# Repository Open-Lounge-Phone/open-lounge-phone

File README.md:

# Open Lounge Phone

A free, open-source, screen-free phone. Real mechanical keys, a handset, and nothing else: no
browser, no feeds, no strangers.

It is a lot more than one phone. Everything runs on **connections**: you sign in on a public
hub you trust, or federate your own servers and services, and you choose the level of safety and
security you want at every step, including how available and how visible you are to each person.
The same board and software make a kid's first phone, a desk phone for grown-ups, a shared
Lounge phone, a small office phone system, or (with the labs firmware) a house intercom, a
doorbell and an elder's daily check-in.

- **Kids' phone** — calls only the contacts a guardian approves, respects quiet hours (callers
  get voicemail with a transcript instead of waking anyone up), and its guardian sees when it
  was last online. Kids' phones on the market are closed boxes with a fixed feature list; this
  one is open, so a child can learn how it works and tinker with it as they grow, while the
  phone's rules stay with their guardians until they decide otherwise. When it starts running
  firmware that isn't an official update, its guardians hear about it straight away, and with
  Ask me first it waits for their OK.
- **Voicemail everywhere** — any call that isn't answered (no answer, declined, busy, quiet
  hours, unavailable) goes to a greeting — the standard one, your recorded name, or your own —
  and the message lands in the callee's inbox, across servers too.
- **Lounge phone** — a shared phone anyone in the space takes over as themselves by scanning its
  code and pressing the key it flashes; it forgets them the moment they're done. People from
  other servers can use it too, if the space allows guests.
- **Grown-ups** use the companion app on their own phone or computer, or any old device as a
  phone (`/device/`, add it to the home screen). You choose who can reach you, whether you're
  taking calls right now, and whether your connections see that you're around.
- **Not just a phone** — the labs firmware ([firmware/labs/](firmware/labs/README.md), 0.0.0)
  turns the board into a house intercom, a doorbell or front desk, a dinner's-ready chime, a
  daily check-in for an elder, a Home Assistant panel, a dial-a-story line or a USB macro pad.
  It's the build on the v0.1 dev boards for now (lightly tested; most of its extras so far on a
  computer). Its features come to the phone firmware later, where they make sense.

Run it on **your own Cloudflare account** or **self-host it with Docker**; to just try it, use the
free public hub at [hub.openloungephone.app](https://hub.openloungephone.app). Your keys and your
server are yours: nothing depends on this project ([security model](docs/security-model.md)). Servers connect to each other, so everyone can reach everyone: you
knock on someone's address (`name@server`), and once they accept you can call. Nobody —
including this project — sits in the middle of your calls, and there is no bridge to the phone
network, ever.

## Status

The software works end to end today. The hardware has its first **early dev board prototype**:
[hardware v0.1](https://github.com/Open-Lounge-Phone/open-lounge-phone/releases/tag/hw-v0.1) (rev A), ordered from JLCPCB on 2026-09-30. Its files are in that release. **Board v0.3 is coming soon** as a fully assembled board or a bare PCB; [join the interest list](https://github.com/Open-Lounge-Phone/open-lounge-phone/discussions/1).

| Phase | What | State |
|---|---|---|
| M0–M4 | Protocol and core logic; self-hosted server, browser phone, companion app; Cloudflare backend; invites, passkeys, voicemail with transcripts | done |
| Lounge | QR takeover with a key-press proof, ephemeral sessions, "open to chat" | done (software) |
| Security (software) | Four-word device fingerprint (phone MENU → About, pairing, the phone's page); phone page with last seen, software version and remove-and-wipe; retention defaults and transcription on/off per space; an audit trail in every space (who changed what, never what was said; read only by those who run the space) | done (software) |
| Recording (C2) | Opt-in per space (never with kids' phones), always announced to every party (spoken prompt, the phone's status light and `REC` on its display, a mark in the apps, other servers too), made by the recording side's own client and uploaded, in the timeline and call log, transcribed only where the space transcribes, expiring with history; other servers may refuse recorded calls | done (software) |
| Device lifecycle | Modes at claim (kids, personal desk phone, Lounge); per-space Lounge session length (idle, end of day, until logout); optional house-line keys and "who's here" on idle Lounge phones (off by default; public lines only for someone signed in); a space's name and time zone can be changed later (Settings), and the phones follow at once; remove = the phone wipes itself | done (server, apps, browser phone); firmware: remove = wipe done, modes and factory reset later |
| P1 / P1b | Accounts and handles (`name@server`), several households per account, open sign-up; spaces (home, team, organization); handles reserved 90 days; recovery codes, session list and sign out everywhere, space owners and leaving (0.5.0) | done |
| P2 | Connections ("buddies"): knock, accept, decline, block — on one server and across servers (signed server-to-server requests) | done |
| P3 | Calls across servers, voicemail, opt-in presence, Lounge guests from other servers | done |
| P4 | The public hub: free, donation-funded, fair-use allowance, Turnstile, operator view, export and account deletion | **live** at hub.openloungephone.app (2026-09-29) |
| Voicemail everywhere | Unanswered calls go to voicemail for every caller and callee (people, kids' phones, Lounge guests, other servers); greetings (standard, recorded name, custom); ring time; recording the greeting on the phone | done (software) |
| P2b | Buddy timeline: per-connection history of calls and voicemails (with transcripts), expiring per connection or by your default (30 days / 1 year / forever); no text chat | done (software) |
| M5 | One-command CLI, `npx openloungephone`: `deploy cloudflare` (prompts, preflight, summary; keys never echoed), `selfhost init` (compose.yaml + .env with random secrets, optional coturn/LiveKit), `status <url>`, `doctor` | done; the desktop (Tauri) app was dropped — the installable web apps cover it |
| P3.5 | Rooms: party lines (always open, or at set hours that ring the members' phones at opening), phone rooms with addresses (`standup@host`, dialable from any phone's key), host mute/remove/lock, cross-server join; hold, instant 3-way (Add caller → Merge) and blind/attended transfer; a peer-to-peer mesh (≤ 4) or a relay (Cloudflare Realtime SFU, or LiveKit when self-hosting) with top-3 forwarding, idle drop and fair-use metering | done (software); relayed rooms are encrypted in transit, end-to-end (SFrame) planned |
| P6 (C1) | Team and org spaces as a workplace phone system: owner/admin/member roles, searchable directory, extensions (companion and phone MENU → Dial ext), ring groups (simultaneous, sequential, round robin), business hours with after-hours actions, shared voicemail boxes ("heard by"), call log with CSV export, audit trail, transfer across households and servers inside the space; public lines (a ring group with its own address anyone may call without connecting, with a queue, voicemail and "call me back"; a call back nobody took shows on the phones as a missed call) ([docs/workplace.md](docs/workplace.md)) | done (software) |
| Calls (0.7.0) | Mute on the phones (MENU 3) and M in the app; a mic check and microphone/speaker choice in the app; reconnecting with an ICE restart, a plain "connection lost" and a poor-connection note; call waiting; missed calls (kept per person or phone, on the phones' MENU 5 and the app's Home) with call back and redial ([docs/phone-ux.md](docs/phone-ux.md)) | done (server, apps, browser phone, firmware 0.9.4; firmware tried in QEMU, not yet on a real board) |
| Notices | A space's guardians (owner and admins in a team) post a short notice to its phones ("Bus is here"), with an optional recording: a chime and the text on the ready screen, lifting the handset plays it, a key clears it; it expires (an hour by default) ([docs/notices.md](docs/notices.md)) | done (server, apps, browser phone, firmware; not yet on a real board) |
| Add-ons | Any service that serves live voice over a call (an assistant, a radio, a notes taker), linked to your own account with an address on it, `you+radio@host`: it links like a phone pairs, says what it does (shown on its page in the app's Add-ons tab), and only you can call it at that address; parts it offers for sharing you give to people, who call that part at its own address `you+radio+listen@host` (here or on other servers) and can stop its calls or give it back. Every add-on is treated as untrusted: an allow-list of messages, limits on calls and lines, calls marked as an add-on's everywhere, kids' phones never reached; off unless the server's operator turns them on (`ADDONS=on`). The add-on bridge ([sdk/python](sdk/python/README.md), Python, Apache-2.0) gives a service the calls as events and PCM audio, with echo and one-way radio examples ([docs/add-ons.md](docs/add-ons.md)) | done (server, apps, browser phone, bridge, sharing; the hardware phone shows the label, not the share, and is not yet tested on a real board) |
| P5 | Interop tests in CI (two self-hosted servers and two Workers under `wrangler dev`, on every push) and a versioned federation spec, [docs/federation-spec.md](docs/federation-spec.md) | done |
| Versions | Servers advertise their software, federation versions and features and negotiate per peer (degrading in plain words); phones and servers exchange protocol ranges (`UPDATE NEEDED` on a too-old phone); v1 frozen by conformance vectors (`tests/conformance/`); CI runs this server against the previous release (`server-v*`) both ways | done |
| Firmware | ESP32-S3 firmware ([firmware/](firmware/README.md), ESP-IDF; changes in [firmware/CHANGELOG.md](firmware/CHANGELOG.md)): Wi-Fi and server setup from a phone, pairing, calls with two-way audio (Opus wideband, PCMU fallback, AGC, concealment, sidetone, echo measurement and canceller: [docs/audio.md](docs/audio.md)), leaving and playing voicemail, hold and transfer, extensions, Lounge phones, signed updates (off in source builds), encrypted storage, the phone check and self-test. The labs build ([firmware/labs/](firmware/labs/README.md), 0.0.0) adds the experiments above | 0.9.6: call audio (Opus at 16 kHz, the mic's AGC, an adaptive jitter buffer and concealment, sidetone, echo test and canceller). 0.9.5: the wired network on hw v0.2. 0.9.4: mute, call waiting, missed calls and redial, reconnecting; the house intercom (signed and encrypted on the LAN), the chime and the daily check-in moved in from labs. Host tests, builds and QEMU tests ([firmware/CHANGELOG.md](firmware/CHANGELOG.md)); not yet on a real board. The v0.1 dev boards run the experimental labs build (0.0.0) for now, lightly tested; full testing waits on the Wi-Fi antennas ([hardware/BRINGUP.md](hardware/BRINGUP.md)) |
| Hardware | A minimal 2-layer board (ESP32-S3, 12 hot-swap keys + hook switch, a 2.13" e-paper display module on a header, 3.5 mm jack + codec for an analog handset, piezo ringer, one status LED; USB-C power, no battery, NFC, speaker or hardware mute) in a 3D-printable base | **v0.1 early dev board prototype** ([`hw-v0.1`](https://github.com/Open-Lounge-Phone/open-lounge-phone/releases/tag/hw-v0.1), rev A): four phones built and working, lightly tested; expect a revision (we recommend board v1.0 for building your own); 3D-printable cases: the prototype box, a wall unit and the plush desk case |

Versions and changes: the server and apps in [CHANGELOG.md](CHANGELOG.md) (releases are tagged
`server-vX.Y.Z`), the firmware in [firmware/CHANGELOG.md](firmware/CHANGELOG.md) (`fw-vX.Y.Z`), the
hardware as `hw-vX.Y` releases; how they fit together:
[openloungephone.app/project/versions/](https://openloungephone.app/project/versions/).

More: [architecture](docs/architecture.md), [the phone's UX](docs/phone-ux.md), [federation](docs/federation.md) (and its
[spec](docs/federation-spec.md)),
[the public hub](docs/hub.md), [add-ons](docs/add-ons.md), [privacy](docs/privacy.md), [hardware](hardware/README.md).

## Layout

```
packages/protocol    wire protocol (zod schemas) — the contract every device speaks
packages/core        pure domain logic shared by all backends and devices
packages/db          SQL migrations + typed store (Cloudflare D1 and SQLite)
packages/federation  server-to-server signatures (RFC 9421, Ed25519), keys, /fed/v1 schemas
packages/server-app  backend-agnostic HTTP API, connection gateway, household hubs, federation
packages/client      browser helpers: socket, WebRTC call media, tones
apps/server-selfhost Node server (+ Dockerfile, compose.yaml with coturn)
apps/server-cloudflare Worker + Durable Objects + D1 + R2, and the deploy script
apps/cli             `npx openloungephone`: deploy, self-host setup, status, doctor
apps/device-web      the phone in a browser (keys, LEDs, status strip, handset)
apps/companion       companion PWA for guardians, grown-ups and operators
firmware/            ESP32-S3 firmware (ESP-IDF), its simulators, and the labs build (firmware/labs)
hardware/            schematic, board layout and core shell, all as code
docs/                architecture, federation (+ spec), hub, privacy, generated protocol reference
```

## Repositories

| Repository | What |
|---|---|
| [open-lounge-phone](https://github.com/Open-Lounge-Phone/open-lounge-phone) (this one) | the product: software, firmware, hardware sources, docs and tests |
| [website](https://github.com/Open-Lounge-Phone/website) | the project site, [openloungephone.app](https://openloungephone.app), built from this repository's docs |
| [.github](https://github.com/Open-Lounge-Phone/.github) | the GitHub organization profile |

## Try it

```sh
npm install
npm start
```

Open the setup link the server prints, create your household, then open
`http://localhost:8787/device/` in another tab. That's the phone. Press Space to lift its
handset and it reads out a pairing code; enter it in the companion app, then call each other.
To run a real server, `npx openloungephone selfhost init` (Docker; see
[docs/self-hosting.md](docs/self-hosting.md) — the Docker packaging has not been build-tested
yet) or `npx openloungephone deploy cloudflare` (your own Cloudflare account; see
[docs/cloudflare.md](docs/cloudflare.md)). `npx openloungephone doctor` checks this machine.

## Development

Requires Node 22.18+ (it runs the TypeScript sources directly).

```sh
npm install
npm test            # unit tests (including a two-server federation test)
npm run check       # lint + typecheck + tests (what CI runs)
npm run docs:protocol     # regenerate docs/protocol.md after changing packages/protocol
npm run docs:federation   # regenerate docs/federation-spec.md after changing packages/federation
OLP_E2E_CLOUDFLARE=1 npx vitest run tests/e2e/cloudflare.test.ts   # two local Workers (after npm run build)
```

CI runs `npm run check` (including the v1 conformance vectors), both docs drift checks, and the
`Interop` workflow (two self-hosted servers, two Workers under `wrangler dev`, and this server
against the previous release in both directions, federating with each other).

## License

Software: [AGPL-3.0-or-later](LICENSE), except the add-on bridge in [sdk/python](sdk/python/)
([Apache-2.0](sdk/python/LICENSE)), so any service can use it. Hardware designs:
[CERN-OHL-S-2.0](hardware/LICENSE).
If you run a modified Open Lounge Phone server for others, you must share your changes.

Proudly supported by [unsubscribe.llc](https://www.unsubscribe.llc/).

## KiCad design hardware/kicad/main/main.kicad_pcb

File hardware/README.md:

# Hardware (in design)

The **minimal board**: an ESP32-S3 module, one USB-C port for power
and flashing, one 3.3 V regulator, 12 hot-swap MX keys and a hook switch wired straight to
GPIOs, a socket for a ready-made 2.13" e-paper display module, a 3.5 mm jack with an ES8311
codec for an off-the-shelf analog handset, a piezo ringer and one status LED. 53 parts on a
2-layer board. It has **no** battery, NFC, speaker, per-key LEDs, hardware mute switch or mic
lights.

Board v0.2 (designed, not built): the same board plus an RJ45 with PoE (W5500, isolated
802.3af module), DRC clean; DESIGN.md §12a.

Status: **schematic done and checked (M1)**, **placement done (M2)**: 156 × 88 mm, all SMD on
the bottom, DRC clean, image in `build/review/placement.png` (`make placement`); **routed
(M3)**: 2 layers, DRC clean, `make fab` writes Gerbers, JLC BOM/CPL and previews to
`build/main/fab/` (DESIGN.md §9a). Nothing ordered yet.

- [DESIGN.md](DESIGN.md): the design, GPIO map, cost, what the board does and doesn't do, and
  the placement (§9) and the questions still open.
- [SCHEMATIC.md](SCHEMATIC.md): the schematic as code (SKiDL, `schematic/`) and its checks.
- [REQUIREMENTS.md](REQUIREMENTS.md) and [BOARD_REQUIREMENTS.md](BOARD_REQUIREMENTS.md): the
  requirements and the 2-layer layout checklist.
- [components/](components/README.md): one file per part, with datasheet pages.
- [GUIDELINES.md](GUIDELINES.md): the design rules (child-safe, rugged, simple).
- [ASSEMBLY.md](ASSEMBLY.md): building the board (PCBA or by hand).
- [sim/](sim/README.md): the regulator simulation (`make sim`).
- Cases, all code in `enclosure/`:
  - [enclosure/PROTO_BOX.md](enclosure/PROTO_BOX.md): the core shell (tray, lid, bezel, a hinged
    handset cradle) for the placed board and what designs built around it must keep.
  - [enclosure/PLUSH.md](enclosure/PLUSH.md): the cushion desk case.
  - [enclosure/FLATCASE.md](enclosure/FLATCASE.md): the laser-cut desk phone (one sheet of 3 mm
    acrylic or plywood, M3 standoffs, the core shell's hinged cradle).

## Building the outputs

Everything here is source; generated outputs are not committed. With Python 3:

```sh
cd hardware
make build     # ERC + design checks -> build/main/ (netlist, BOM, checks, cost, part count)
make review    # readable schematic PDF -> build/review/schematic.pdf
make sim       # regulator simulation -> build/sim/report.md (ngspice or KiCad's libngspice)
make placement # KiCad 10: kicad/main board, DRC, wiring metrics, build/review/placement.png
make proto     # core shell (enclosure/) + its fit checks
```

`layout/`: `place.py` builds `kicad/main/main.kicad_pcb` from the netlist (placement table +
a small placer for resistors and capacitors), `review_placement.py` measures it and draws the
placement image (planned lanes live only in the image), plus the netlist reader, fab-output
export and the project footprint library (hot-swap socket, board marking).

Hardware designs in this directory are licensed under the
[CERN Open Hardware Licence v2 – Strongly Reciprocal](LICENSE).

## Power

- **Rev A (hw v0.1) boards:** USB-C only.
- **v0.2 boards:** a USB-C charger, or one Ethernet cable from a PoE switch port or a PoE
  injector that follows IEEE 802.3af or 802.3at. Network and power then come on that one cable,
  up to 100 m. Plugging in both is fine: PoE takes over.
- **Use a real charger or PoE.** A computer's USB port is only for debugging (flashing and the
  console), and only with the PoE cable plugged in too, so PoE carries the load. A computer port
  on its own isn't a supported power source: at moments the phone uses its cable and Wi-Fi
  together and draws more than such a port's 500 mA.
- **"Passive" PoE injectors** (the 24 V kind) won't power it.
- **USB-C is still how you flash it** and read its console, on either board.

The numbers behind this (DESIGN.md §12a, `schematic/power_budget.yaml`): the board draws at most
618 mA at 5 V, of the PoE module's 1400 mA; the module asks for at least 100 mA, and the phone
draws more than that in every network mode; it is an 802.3af class 0 device (any 802.3af or
802.3at port powers it).

## Versions

| Tag | What | Date |
|---|---|---|
| [`hw-v0.1`](https://github.com/Open-Lounge-Phone/open-lounge-phone/releases/tag/hw-v0.1) | Minimal board, silkscreen **rev A**: the first board ordered from JLCPCB. The release holds the exact Gerbers, BOM/CPL, schematic and layer PDFs, STEP, and the build guide | 2026-09-30 |
| v0.2 (not tagged) | The wired revision: the minimal board plus an **RJ45 with PoE** (W5500 on SPI, isolated 802.3af module, USB/PoE diode-OR), silkscreen **v0.2**; the proto box gets a hood over the RJ45 (DESIGN.md §12a). Not ordered | 2026-10-15 |

Hardware releases are tagged `hw-vX.Y`; firmware releases are tagged `fw-vX.Y.Z`. A board revision
gets a new `hw-` tag and a new silkscreen rev letter, and the fab files for a tag come from that
tag's release, not from a fresh `make fab` (the router isn't byte-for-byte deterministic yet).
Phones never follow GitHub's "latest release" (which can be a hardware release): official
firmware takes updates from the fixed `fw-stable` release, one manifest per board, signed and
naming the board it is for (`minimal-revA` = `hw-v0.1`: `firmware-manifest.json`; `minimal-v02`
= hw v0.2: `firmware-manifest-minimal-v02.json`); firmware built from source has updates
off until you add your own key. See `firmware/README.md` "Updates" and "Your keys, your server".

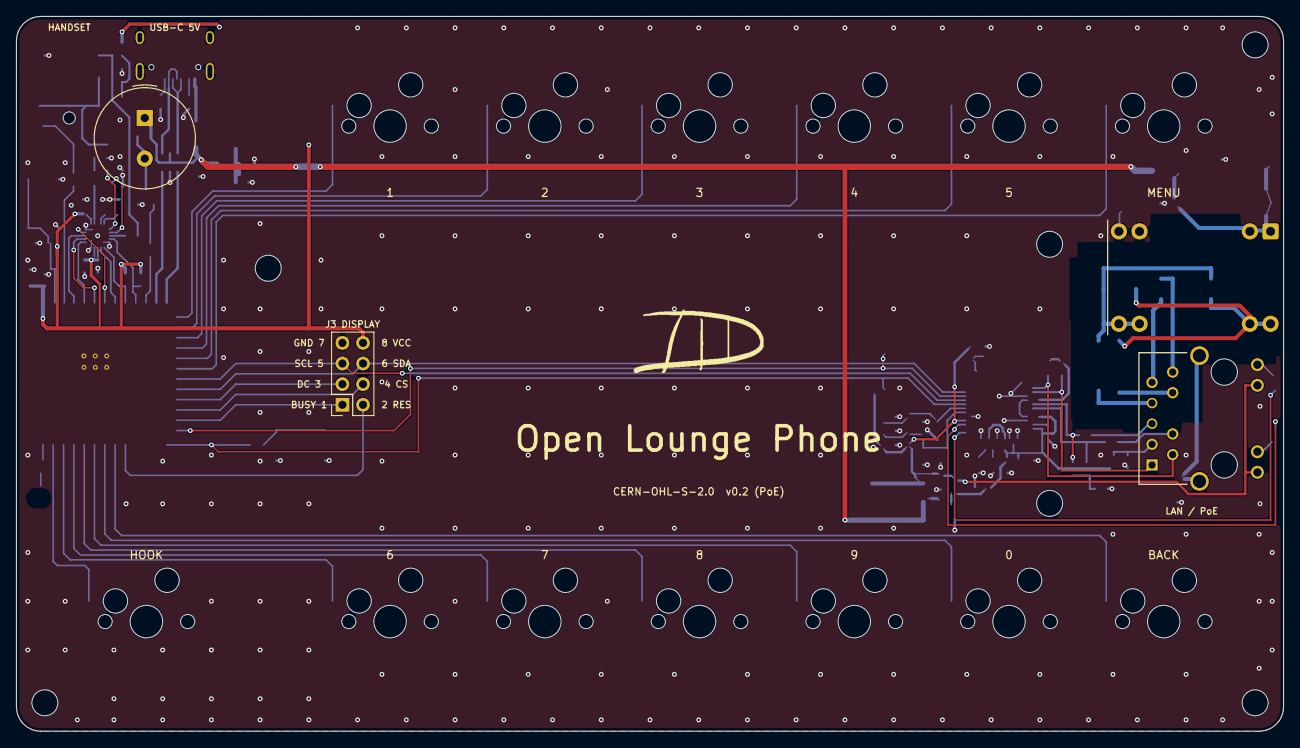
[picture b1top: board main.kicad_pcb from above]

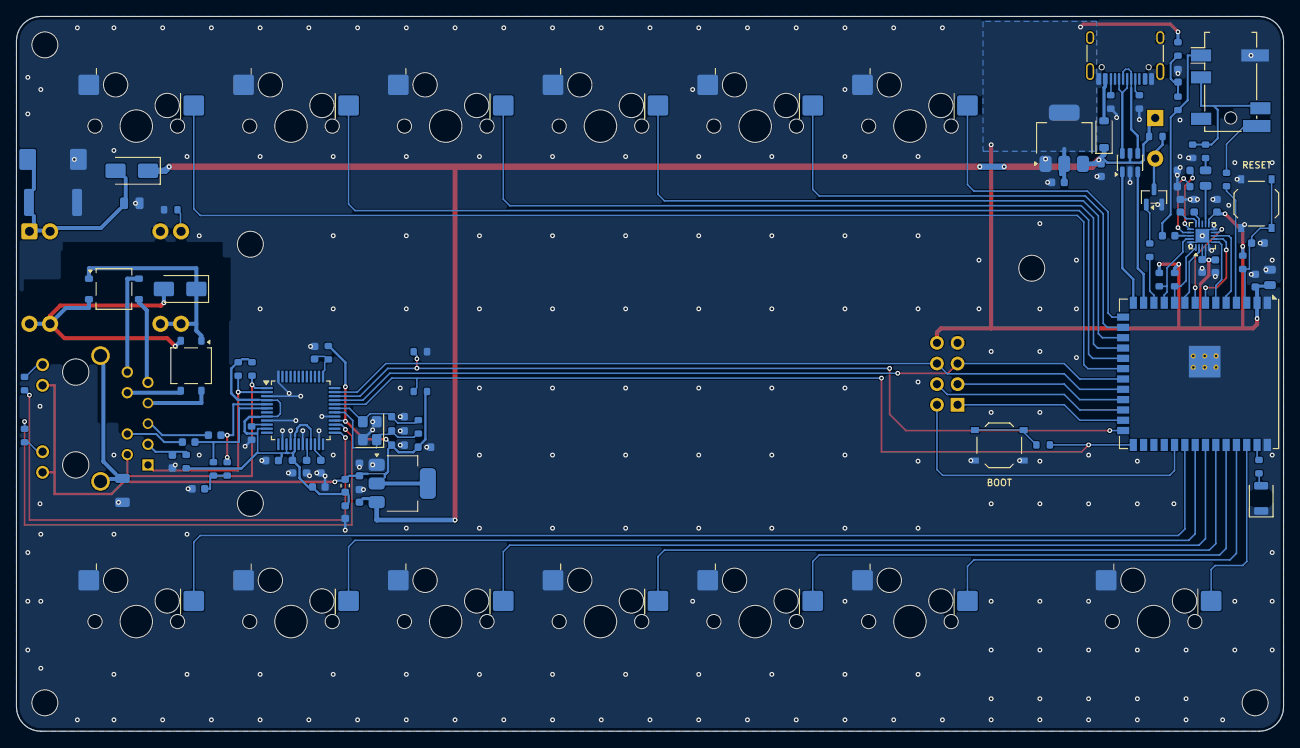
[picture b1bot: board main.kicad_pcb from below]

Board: 2 copper layers, 156.0 x 88.0 mm, 107 parts (95 on the bottom side), 85 nets.

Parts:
BR1, BR2: MB10S-50MIL; TO-269AA
BZ1: PS1240P02BT; Buzzer_TDK_PS1240P02BT_D12.2mm_H6.5mm
C1, C16, C24, C28: 4.7uF 16V X5R; C_0603_1608Metric
C2, C17: 2.2uF 16V X5R; C_0603_1608Metric
C3, C12: 22uF 25V X5R; C_0805_2012Metric
C4, C6, C7, C19, C21, C22, C23, C32: 100nF 50V X7R; C_0603_1608Metric
C5, C8, C9, C10, C11, C14, C15: 1uF 50V X5R; C_0603_1608Metric
C13, C18, C20: 10uF 10V X5R; C_0603_1608Metric
C25, C31: 10nF 50V X7R; C_0603_1608Metric
C26, C27: 18pF 50V C0G; C_0603_1608Metric
C29, C30: 6.8nF 50V X7R; C_0603_1608Metric
C33: 1nF 2kV X7R; C_1206_3216Metric
C34: CA45-D-16V-100uF-K; CP_EIA-7343-31_Kemet-D
C35: 10uF 25V X5R; C_0805_2012Metric
D1: USBLC6-2SC6; SOT-23-6
D2: LTST-C230KRKT; LED_1206_3216Metric_ReverseMount_Hole1.8x2.4mm
D3: B5819W SL; D_SOD-123
D4: SMAJ58A; D_SMA
D5: SS34; D_SMA
FB1: GZ1608D601TF; L_0603_1608Metric
G1: signature logo; openloungephone_logo_F
G2: Open Lounge Phone; openloungephone_name_F
H1, H2, H3, H4: M3 mounting hole; MountingHole_3.2mm_M3
H5, H6: M3 display standoff; MountingHole_3.2mm_M3
J1: TYPE-C-31-M-12; USB_C_Receptacle_HRO_TYPE-C-31-M-12
J2: PJ-31060; Jack_3.5mm_PJ31060-I_Horizontal
J3: HX PM2.54-2x4P ZC; PinSocket_2x04_P2.54mm_Vertical
J4: HR871150C; RJ45_HanRun_HR871150C
PS1: DP9900LP-5V; Converter_DCDC_Silvertel_Ag99xxLP_THT
Q1: MMBT3904; SOT-23
R1, R2: 5.1k; R_0603_1608Metric
R3, R17, R18, R19: 10k; R_0603_1608Metric
R4, R5, R7: 4.7k; R_0603_1608Metric
R6: 22; R_0603_1608Metric
R8, R10, R11, R12, R13, R14: 1k; R_0603_1608Metric
R9: 2.2k; R_0603_1608Metric
R15: 12.4k; R_0603_1608Metric
R16: 1M; R_0603_1608Metric
R20, R21, R22, R23: 49.9; R_0603_1608Metric
R24: 10; R_0603_1608Metric
R25, R26: 330; R_0603_1608Metric
R27: 100k; R_0603_1608Metric
R28: 51; R_2512_6332Metric
SW1, SW2: TS-1187A-B-A-B; SW_Push_1P1T_XKB_TS-1187A
SW3, SW4, SW5, SW6, SW7, SW8, SW9, SW10, SW11, SW12, SW13, SW14, SW15: CPG151101S11-2; Kailh_MX_Hotswap_CPG151101S11
U1: ESP32-S3-WROOM-1U-N16R8; ESP32-S3-WROOM-1U
U2, U5: SGM2212-3.3XKC3G/TR; SOT-223-3_TabPin2
U3: ES8311; QFN-20-1EP_3x3mm_P0.4mm_EP1.65x1.65mm
U4: W5500; LQFP-48_7x7mm_P0.5mm
Y1: X322525MOB4SI; Crystal_SMD_3225-4Pin_3.2x2.5mm

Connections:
3V3: C2.1, C3.1, C4.1, C6.1, C7.1, C8.1, J3.8, R3.2, R4.2, R5.2, R8.1, U1.2, U2.2, U3.3, U3.4, U3.11
BOOT_SW: R14.2, SW2.1
BUZZER: R12.1, U1.12
BUZZER_B: Q1.1, R12.2
BUZZER_DRV: BZ1.2, Q1.3, R11.2
CC1: J1.A5, R1.1
CC2: J1.B5, R2.1
DAC_OUTP: C12.1, U3.12
EAR_AC: C12.2, R6.1
EN: C5.1, R3.1, SW1.1, U1.3
EPD_BUSY: J3.1, U1.25
EPD_CLK: J3.5, U1.21, U4.33
EPD_CS: J3.4, U1.24
EPD_DC: J3.3, U1.23
EPD_DIN: J3.6, U1.22, U4.35
EPD_RST: J3.2, U1.31
ES8311_ADCVREF: C10.1, U3.15
ES8311_DACVREF: C11.1, U3.14
ES8311_VMID: C9.1, U3.16
ETH_3V3: C17.1, C18.1, C19.1, FB1.1, J4.11, J4.13, R17.2, R19.2, U4.28, U5.2
ETH_3V3A: C20.1, C21.1, C22.1, C23.1, FB1.2, R20.2, R21.2, R24.1, U4.4, U4.8, U4.11, U4.15, U4.17, U4.21
ETH_ACTLED: R26.2, U4.27
ETH_CS: R14.1, R17.1, U1.27, U4.32
ETH_CT: C32.1, J4.3, R24.2
ETH_LED_ACTIVITY_K: J4.12, R26.1
ETH_LED_LINK_K: J4.14, R25.1
ETH_LINKLED: R25.2, U4.25
ETH_MISO: R18.1, U1.26, U4.34
ETH_RDN_J: C30.1, J4.5
ETH_RDP_J: C29.1, J4.4
ETH_RST: C28.1, R19.1, U4.37
ETH_RXC: C31.1, R22.2, R23.2
ETH_RXN: C30.2, R23.1, U4.5
ETH_RXP: C29.2, R22.1, U4.6
ETH_SHIELD: C33.1, J4.SH
ETH_TXN: J4.2, R21.1, U4.1
ETH_TXP: J4.1, R20.1, U4.2
GND: C1.2, C2.2, C3.2, C4.2, C5.2, C6.2, C7.2, C8.2, C9.2, C10.2, C11.2, C13.2, C15.2, C16.2, C17.2, C18.2, C19.2, C20.2, C21.2, C22.2, C23.2, C24.2, C25.2, C26.2, C27.2, C28.2, C31.2, C32.2, C33.2, C34.2, C35.2, D1.2, D2.1, J1.A1, J1.A12, J1.B1, J1.B12, J1.SH, J2.R2, J3.7, PS1.3, Q1.2, R1.2, R2.2, R7.2, R15.2, R18.2, R27.2, R28.2, SW1.2, SW2.2, SW3.2, SW4.2, SW5.2, SW6.2, SW7.2, SW8.2, SW9.2, SW10.2, SW11.2, SW12.2, SW13.2, SW14.2, SW15.2, U1.1, U1.40, U1.41, U2.1, U3.5, U3.10, U3.20, U3.21, U4.3, U4.9, U4.14, U4.16, U4.19, U4.23, U4.29, U4.48, U5.1, Y1.2, Y1.4
HOOK: SW15.1, U1.38
HS_DET: J2.TN, R10.1
HS_EAR: J2.R1, J2.T, R6.2, R7.1
HS_MIC: C14.1, J2.S, R9.2
I2C_SCL: R5.1, U1.10, U3.1
I2C_SDA: R4.1, U1.11, U3.19
I2S_BCLK: U1.6, U3.6
I2S_DIN: U1.7, U3.7
I2S_DOUT: U1.8, U3.9
I2S_MCLK: U1.9, U3.2
I2S_WS: U1.5, U3.8
JACK_DET: R10.2, U1.4
KEY_0: SW13.1, U1.33
KEY_1: SW3.1, U1.15
KEY_2: SW4.1, U1.16
KEY_3: SW5.1, U1.17
KEY_4: SW6.1, U1.18
KEY_5: SW7.1, U1.19
KEY_6: SW9.1, U1.37
KEY_7: SW10.1, U1.36
KEY_8: SW11.1, U1.35
KEY_9: SW12.1, U1.34
KEY_BACK: SW14.1, U1.32
KEY_MENU: SW8.1, U1.20
MIC1N: C15.1, U3.17
MIC1P: C14.2, U3.18
MIC_BIAS: C13.1, R8.2, R9.1
POE_5V: C34.1, C35.1, D5.2, PS1.1, PS1.2, R28.1
POE_ADJ: PS1.4, R27.1
POE_VA1: BR1.4, J4.7
POE_VA2: BR1.3, J4.8
POE_VB1: BR2.3, J4.9
POE_VB2: BR2.4, J4.10
POE_VIN_N: BR1.2, BR2.2, D4.2, PS1.7, PS1.8
POE_VIN_P: BR1.1, BR2.1, D4.1, PS1.5, PS1.6
STATUS_LED: R13.1, U1.39
STATUS_LED_A: D2.2, R13.2
USB_DN: D1.3, D1.4, J1.A7, J1.B7, U1.13
USB_DP: D1.1, D1.6, J1.A6, J1.B6, U1.14
V5: BZ1.1, C1.1, C16.1, D1.5, D3.1, D5.1, R11.1, U2.3, U5.3
VBUS: D3.2, J1.A9, J1.B4
VBUS_W: J1.A4, J1.B9
W5500_1V2O: C25.1, U4.22
W5500_EXRES: R15.1, U4.10
W5500_TOCAP: C24.1, U4.20
W5500_XI: C26.1, R16.1, U4.30, Y1.1
W5500_XO: C27.1, R16.2, U4.31, Y1.3

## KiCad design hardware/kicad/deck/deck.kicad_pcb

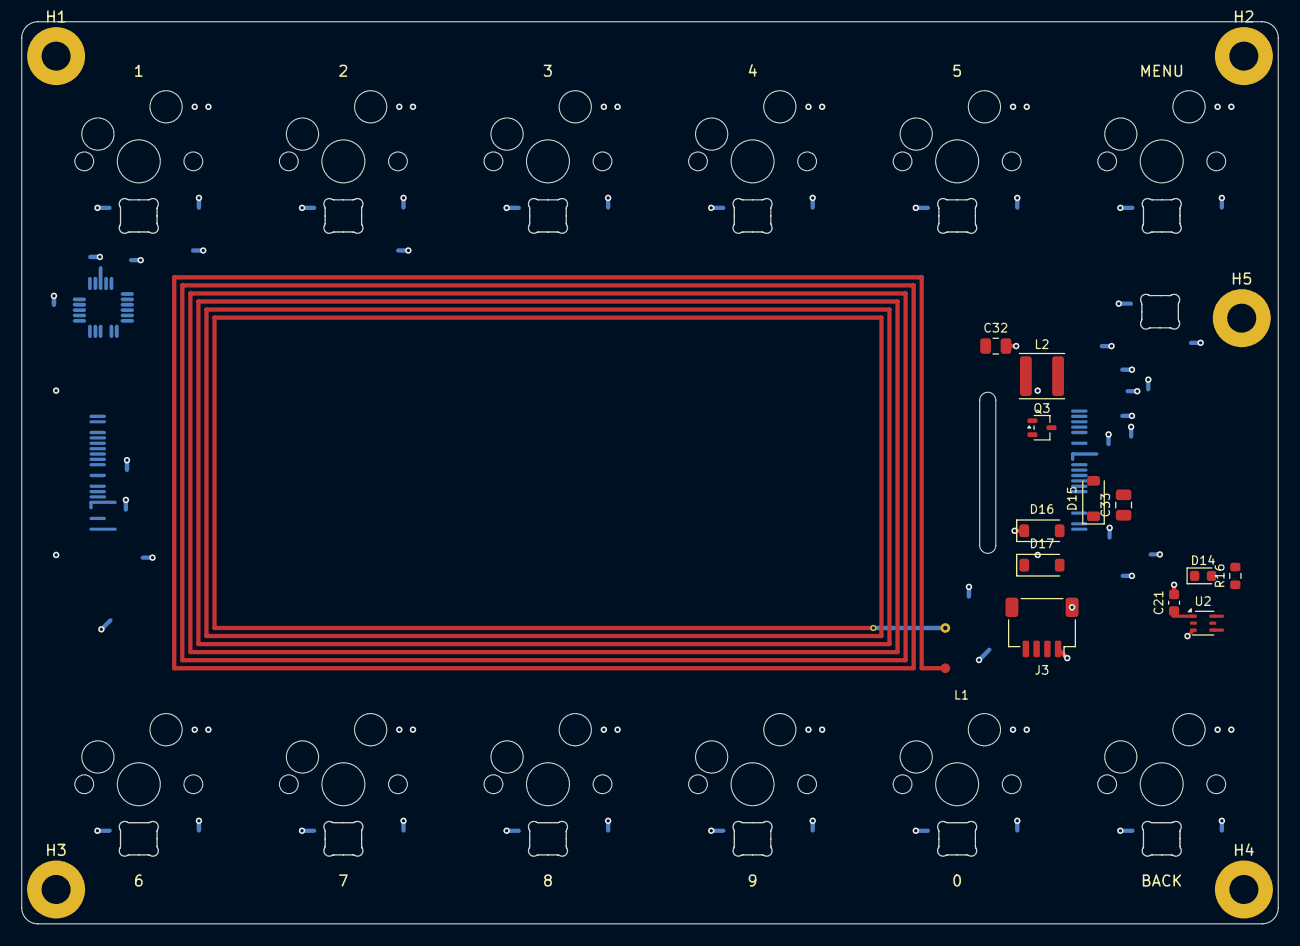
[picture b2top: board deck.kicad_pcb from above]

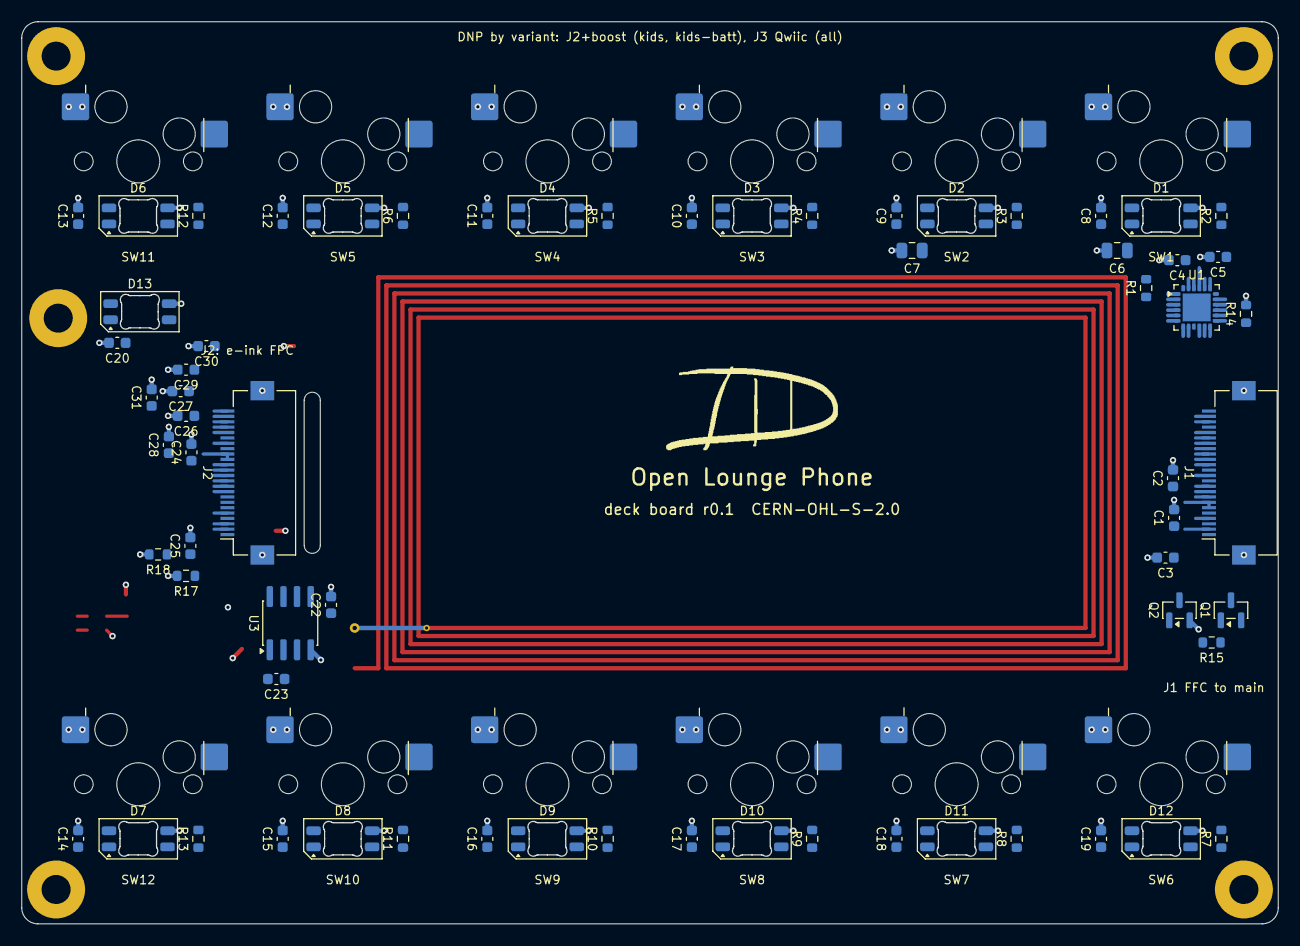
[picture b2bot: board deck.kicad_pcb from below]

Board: 4 copper layers, 117.0 x 84.0 mm, 97 parts (79 on the bottom side), 59 nets.

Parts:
C1, C3: 10uF 10V X5R; C_0603_1608Metric
C2, C4, C5, C8, C9, C10, C11, C12, C13, C14, C15, C16, C17, C18, C19, C20, C22: 100nF 50V X7R; C_0603_1608Metric
C6, C7: 22uF 25V X5R; C_0805_2012Metric
C21, C24, C25, C26, C27, C28, C29, C30, C31: 1uF 50V X5R; C_0603_1608Metric
C23: 22pF 50V C0G; C_0603_1608Metric
C32, C33: 4.7uF 25V X5R; C_0805_2012Metric
D1, D2, D3, D4, D5, D6, D7, D8, D9, D10, D11, D12, D13: SK6812MINI-E; LED_SK6812MINI-E_3.2x2.8mm_P1.5mm_ReverseMount
D14: KT-0603R; LED_0603_1608Metric
D15, D16, D17: MBR0530T1G; D_SOD-123
G1: openloungephone_logo_B
H1, H2, H3, H4, H5: M2.5; MountingHole_2.7mm_M2.5_Pad
J1, J2: FH12-24S-0.5SH(55); Hirose_FH12-24S-0.5SH_1x24-1MP_P0.50mm_Horizontal
J3: SM04B-SRSS-TB(LF)(SN); JST_SH_SM04B-SRSS-TB_1x04-1MP_P1.00mm_Horizontal
L1: PCB coil (copper); NFC_Coil_Strip
L2: SWPA4020S470MT; L_Sunlord_SWPA4020S
Q1: AO3401A; SOT-23
Q2: AO3400A; SOT-23
Q3: SI1308EDL-T1-GE3; SOT-323_SC-70
R1, R2, R3, R4, R5, R6, R7, R8, R9, R10, R11, R12, R13: 10k; R_0603_1608Metric
R14, R15: 100k; R_0603_1608Metric
R16: 470; R_0603_1608Metric
R17: 1M; R_0603_1608Metric
R18: 2.2; R_0603_1608Metric
SW1, SW2, SW3, SW4, SW5, SW6, SW7, SW8, SW9, SW10, SW11, SW12: CPG151101S11-2; Kailh_MX_Hotswap_CPG151101S11
U1: AW9523BTQR; TQFN-24-1EP_4x4mm_P0.5mm_EP2.6x2.6mm
U2: LTR-303ALS-01; Lite-On_LTR-303ALS-01
U3: ST25DV04K-IER6S3; SOIC-8_3.9x4.9mm_P1.27mm

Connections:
3V3: C1.1, C2.1, C5.1, C21.1, C22.1, C24.1, C32.1, J1.6, J1.7, J2.15, J2.16, J3.2, L2.1, R1.2, R2.2, R3.2, R4.2, R5.2, R6.2, R7.2, R8.2, R9.2, R10.2, R11.2, R12.2, R13.2, R16.1, U1.21, U2.1, U3.8
AW_RSTN: C4.1, R1.1, U1.23
EPD_BUSY: J1.8, J2.9
EPD_CP: C33.2, D16.2, D17.1
EPD_CS: J1.15, J2.12
EPD_DC: J1.10, J2.11
EPD_GDR: J2.2, Q3.1, R17.1
EPD_MOSI: J1.14, J2.14
EPD_PREVGH: C31.1, D15.1, J2.21
EPD_PREVGL: C29.1, D17.2, J2.23
EPD_RESE: J2.3, Q3.2, R18.1
EPD_RST: J1.9, J2.10
EPD_SCK: J1.12, J2.13
EPD_SW: C33.1, D15.2, L2.2, Q3.3
EPD_VCOM: C30.1, J2.24
EPD_VDD: C26.1, J2.18
EPD_VSH1: C27.1, J2.20
EPD_VSH2: C25.1, J2.5
EPD_VSL: C28.1, J2.22
GND: C1.2, C2.2, C3.2, C4.2, C5.2, C6.2, C7.2, C8.2, C9.2, C10.2, C11.2, C12.2, C13.2, C14.2, C15.2, C16.2, C17.2, C18.2, C19.2, C20.2, C21.2, C22.2, C24.2, C25.2, C26.2, C27.2, C28.2, C29.2, C30.2, C31.2, C32.2, D1.3, D2.3, D3.3, D4.3, D5.3, D6.3, D7.3, D8.3, D9.3, D10.3, D11.3, D12.3, D13.3, D16.1, H1.1, H2.1, H3.1, H4.1, H5.1, J1.3, J1.5, J1.11, J1.13, J1.21, J1.24, J1.MP, J2.8, J2.17, J2.MP, J3.1, J3.MP, Q2.2, R14.2, R17.2, R18.2, SW1.2, SW2.2, SW3.2, SW4.2, SW5.2, SW6.2, SW7.2, SW8.2, SW9.2, SW10.2, SW11.2, SW12.2, U1.9, U1.18, U1.24, U1.25, U2.3, U3.4
I2C_SCL: J1.16, J3.4, U1.19, U2.4, U3.6
I2C_SDA: J1.17, J3.3, U1.20, U2.6, U3.5
IRQ: J1.18, U1.22, U3.7
KEY_0: R11.1, SW10.1, U1.2
KEY_1: R2.1, SW1.1, U1.5
KEY_2: R3.1, SW2.1, U1.6
KEY_3: R4.1, SW3.1, U1.7
KEY_4: R5.1, SW4.1, U1.8
KEY_5: R6.1, SW5.1, U1.10
KEY_6: R7.1, SW6.1, U1.11
KEY_7: R8.1, SW7.1, U1.12
KEY_8: R9.1, SW8.1, U1.13
KEY_9: R10.1, SW9.1, U1.1
KEY_BACK: R13.1, SW12.1, U1.17
KEY_MENU: R12.1, SW11.1, U1.16
LED_D1: D1.2, D2.4
LED_D2: D2.2, D3.4
LED_D3: D3.2, D4.4
LED_D4: D4.2, D5.4
LED_D5: D5.2, D6.4
LED_D6: D6.2, D7.4
LED_D7: D7.2, D8.4
LED_D8: D8.2, D9.4
LED_D9: D9.2, D10.4
LED_D10: D10.2, D11.4
LED_D11: D11.2, D12.4
LED_D12: D12.2, D13.4
LED_DATA_BUF: D1.4, J1.4
LED_PWR_EN: Q2.1, R14.1, U1.15
MUTE_SENSE: J1.20, U1.14
NFC_AC0: C23.1, L1.1, U3.2
NFC_AC1: C23.2, L1.2, U3.3
PRIV_LED_A: D14.2, R16.2
PRIV_LED_K: D14.1, J1.19
VLED: C6.1, C7.1, C8.1, C9.1, C10.1, C11.1, C12.1, C13.1, C14.1, C15.1, C16.1, C17.1, C18.1, C19.1, C20.1, D1.1, D2.1, D3.1, D4.1, D5.1, D6.1, D7.1, D8.1, D9.1, D10.1, D11.1, D12.1, D13.1, Q1.3
VLED_PFET_G: Q1.1, Q2.3, R15.2
VOL_DN: J1.22, U1.3
VOL_UP: J1.23, U1.4
VSYS: C3.1, J1.1, J1.2, Q1.2, R15.1

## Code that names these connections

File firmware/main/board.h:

// Generated by firmware/tools/gen_board.py from hardware/build/main/gpio_map.json.
// Do not edit by hand: change hardware/schematic/pin_table.yaml and regenerate.
// Board: Open Lounge Phone main board, rev v0.2 (rev A + RJ45/PoE); module: ESP32-S3-WROOM-1U-N16R8 (16 MB flash, 8 MB octal PSRAM)
#pragma once

#include "sdkconfig.h"

// Keys: active low with internal pull-ups, in protocol order (index = button index;
// 10 = MENU, 11 = BACK).
#define PIN_KEY_1_HW             3
#define PIN_KEY_2_HW             46
#define PIN_KEY_3_HW             9
#define PIN_KEY_4_HW             10
#define PIN_KEY_5_HW             11
#define PIN_KEY_6_HW             43  // UART0 pin: the simulator build moves it (CONFIG_OLP_SIM)
#define PIN_KEY_7_HW             44  // UART0 pin: the simulator build moves it (CONFIG_OLP_SIM)
#define PIN_KEY_8_HW             42
#define PIN_KEY_9_HW             41
#define PIN_KEY_0_HW             40
#define PIN_KEY_MENU_HW          12
#define PIN_KEY_BACK_HW          39

#define PIN_HOOK                 2  // low = handset on the hook (internal pull-up)
#define PIN_JACK_DET             4  // high = plug in (internal pull-up)
#define PIN_BUZZER               8  // piezo via NPN, ~4 kHz
#define PIN_STATUS_LED           1  // active high
#define PIN_BOOT                 0  // through 1k; also the W5500's CS (hw v0.2)

// hw v0.2 (CONFIG_OLP_BOARD_V02) adds a W5500 on the display's SPI bus. Rev A (hw v0.1,
// the default board) has none: there GPIO0 is only the BOOT button and GPIO45 is free, so a
// rev A build never drives them or looks for the chip.
#if CONFIG_OLP_BOARD_V02
#define BOARD_HAS_ETHERNET       1  // W5500, polled (no INT / RST GPIO)
#define PIN_ETH_CS               0  // 10k pull-up; BOOT through 1k
#define PIN_ETH_MISO             45  // strap GPIO45, 10k pull-down
#define PIN_ETH_SCLK             13  // shared with the display
#define PIN_ETH_MOSI             14  // shared with the display
#else
#define BOARD_HAS_ETHERNET       0
#endif

#define PIN_EPD_CLK              13
#define PIN_EPD_DIN              14
#define PIN_EPD_CS               47
#define PIN_EPD_DC               21
#define PIN_EPD_RST              38
#define PIN_EPD_BUSY             48

#define PIN_I2C_SDA              18
#define PIN_I2C_SCL              17
#define CODEC_I2C_ADDR           0x18  // ES8311
#define PIN_I2S_MCLK             16
#define PIN_I2S_BCLK             6
#define PIN_I2S_WS               5
#define PIN_I2S_DOUT             15  // to the codec (playback)
#define PIN_I2S_DIN              7  // from the codec (record)

// The Wokwi ESP32-S3 prints its console on UART0 (IO43/IO44), where the board has keys 6
// and 7; the simulator build moves those two keys to free pins (no PSRAM in the sim).
#if CONFIG_OLP_SIM
#define PIN_KEY_6 35
#define PIN_KEY_7 36
#else
#define PIN_KEY_6 PIN_KEY_6_HW
#define PIN_KEY_7 PIN_KEY_7_HW
#endif
#define PIN_KEY_1 PIN_KEY_1_HW
#define PIN_KEY_2 PIN_KEY_2_HW
#define PIN_KEY_3 PIN_KEY_3_HW
#define PIN_KEY_4 PIN_KEY_4_HW
#define PIN_KEY_5 PIN_KEY_5_HW
#define PIN_KEY_8 PIN_KEY_8_HW
#define PIN_KEY_9 PIN_KEY_9_HW
#define PIN_KEY_0 PIN_KEY_0_HW
#define PIN_KEY_MENU PIN_KEY_MENU_HW
#define PIN_KEY_BACK PIN_KEY_BACK_HW

#define KEY_COUNT 12
#define KEY_MENU_INDEX 10
#define KEY_BACK_INDEX 11
#define KEY_PINS { PIN_KEY_1, PIN_KEY_2, PIN_KEY_3, PIN_KEY_4, PIN_KEY_5, PIN_KEY_6, PIN_KEY_7, PIN_KEY_8, PIN_KEY_9, PIN_KEY_0, PIN_KEY_MENU, PIN_KEY_BACK }
#define KEY_NAMES { "1", "2", "3", "4", "5", "6", "7", "8", "9", "0", "MENU", "BACK" }

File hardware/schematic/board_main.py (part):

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           USBLC6-2SC6), a Schottky OR of USB VBUS and the PoE 5 V into the 5 V rail V5,
           SGM2212-3.3 LDO (800 mA), bulk + decoupling per the module datasheet.
- mcu:     ESP32-S3-WROOM-1U-N16R8 (U.FL antenna), EN RC reset + RESET button, BOOT on GPIO0.
- keys:    12 MX hot-swap sockets straight to GPIOs (internal pull-ups), plus the hook switch
           (a 13th socket under the hook plunger).
- audio:   ES8311 codec (datasheet reference parts) + 3.5 mm TRRS handset jack (CTIA):
           earpiece on tip + ring 1, mic on sleeve with an RC-filtered bias, insertion detect
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    rst["A"] += n["EN"]
    rst["B"] += GND
    # BOOT: GPIO0 has an internal weak pull-up (p13); the button pulls it low at reset.
    # hw v0.2: GPIO0 is also the W5500's chip select (ETH_CS, 10 k pull-up in ethernet()), so
    # the button reaches it through 1 k: 3.3 V x 1k / 11k = 0.30 V at reset (download mode), and
    # a press while firmware drives CS only costs 3.3 mA.
    sw = n["BOOT_SW"] = Net("BOOT_SW")    # its 1 k series resistor is made in ethernet()
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

def keys(d, n, GND):
    """12 keys + the hook switch, each an MX switch in a hot-swap socket between its GPIO and
    GND. Internal pull-ups; debounce in firmware. The switch contacts sit inside the switch
    housing (not user-reachable), so no series resistors or ESD parts."""
    assert len(KEYS) == d.n_keys
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    series(mic1n, GND, C("1u", note="MIC1N reference (p4)"))

    # insertion detect: TN touches the tip (4.7k to GND) with no plug; a plug lifts it off
    series(det, n["JACK_DET"], R("1k", note="GPIO series (contact reaches the plug)"))


def ui(n, GND, V5, V3V3):
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    h = make("DISPLAY_HDR", ref="J3", note="SPI display module (WeAct 2.9\" plugs in)")
    h["VCC"] += V3V3
    h["GND"] += GND
    for pin, net in (("DIN", "EPD_DIN"), ("CLK", "EPD_CLK"), ("CS", "EPD_CS"), ("DC", "EPD_DC"),
                     ("RST", "EPD_RST"), ("BUSY", "EPD_BUSY")):
        h[pin] += n[net]

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    Straps: SCSn = GPIO0 with a 10 k pull-up (high at reset = SPI boot, and MISO is then Hi-Z,
    W5500 p10); MISO = GPIO45 (VDD_SPI strap, must read low) with a 10 k pull-down."""
    E3, EA = rail("ETH_3V3"), rail("ETH_3V3A")
    series(n["ETH_CS"], n["BOOT_SW"], R("1k", note="BOOT button series (GPIO0 is also ETH_CS)"))
    # own regulator: keeps the W5500's 130 mA off the module's LDO (heat) and its supply clean
    ldo = make("SGM2212-3.3", ref="U5", note="ETH_3V3 LDO (W5500)")
    ldo["VIN"] += V5
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              "RSVD41", "RSVD42", "SPDLED", "DUPLED", "INTn", "PMODE0", "PMODE1", "PMODE2"):
        u[p] += NC
    u["RSVD23"] += GND                       # "must be tied to GND" (p9)
    for pin, net, part in (("EXRES1", "W5500_EXRES", R("12.4k", note="EXRES1 12.4 k 1 % (p11)")),
                           ("TOCAP", "W5500_TOCAP", C("4.7u", note="TOCAP (p8)")),
                           ("1V2O", "W5500_1V2O", C("10n", note="1V2O (p8)"))):
        x = Net(net)
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    u["SCSn"] += n["ETH_CS"]
    u["MISO"] += n["ETH_MISO"]
    series(n["ETH_CS"], E3, R("10k", note="ETH_CS pull-up: high at reset (SPI boot, MISO Hi-Z)"))
    series(n["ETH_MISO"], GND, R("10k", note="ETH_MISO pull-down: GPIO45 strap low at reset"))
    # reset: power-on RC (no free GPIO), longer than the module's EN delay
    rst = Net("ETH_RST")
    u["RSTn"] += rst
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

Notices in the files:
hardware/kicad/deck/deck.kicad_pcb:
Open Lounge Phone - CERN-OHL-S-2.0
deck board r0.1  CERN-OHL-S-2.0
hardware/kicad/main/main.kicad_pcb:
CERN-OHL-S-2.0  v0.2 (PoE)
